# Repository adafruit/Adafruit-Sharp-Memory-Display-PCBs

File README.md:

# PCB for the Adafruit Sharp Memory display breakout board

<br />

[The 96x96 resolution SHARP Memory LCD is no longer made, but we have a higher-resolution 168x144 display available in the shop](https://www.adafruit.com/product/3502).

The 1.3" and 2.7" SHARP Memory LCD displays are a cross between an eInk (e-paper) display and an LCD. They have the ultra-low power usage of eInk and the fast-refresh rates of an LCD. This model has a matt silver background, and pixels show up as little mirrors for a silver-reflective display, a really beautiful and unique look. It does not have a backlight, but it is daylight readable. For dark/night reading you may need to illuminate the LCD area with external LEDs.

The display is 3V powered and 3V logic, so we placed it on a fully assembled & tested breakout board with a 3V regulator and level shifting circuitry. The display slots into a ZIF socket on board and we use a piece of double-sided tape to adhere it onto one side. There are four mounting holes so you can easily attach it to a box.

The display is 'write only' which means that it only needs 3 pins to send data. However, the downside of a write-only display is that the entire 96x96 bits (1,152 bytes) must be buffered by the microcontroller driver. On an Arduino Uno/Leonardo that's half the RAM available and so it might not be possible to run this display with other RAM-heavy libraries like SD interfacing.

Check out [this Learn guide](https://learn.adafruit.com/adafruit-sharp-memory-display-breakout/overview) for details on the boards and usage.

[Then download and install our SHARP Memory Display library](https://github.com/adafruit/Adafruit_SHARP_Memory_Display) and the [Adafruit GFX library](https://github.com/adafruit/Adafruit-GFX-Library). Run the example sharpmemtest sketch with the correct data pins to start drawing lines, circles, rectangles, text, etc!

## License

Adafruit invests time and resources providing this open source design, 
please support Adafruit and open-source hardware by purchasing 
products from Adafruit!

Designed by Adafruit Industries.  
Creative Commons Attribution, Share-Alike license, check license.txt for more information
All text above must be included in any redistribution

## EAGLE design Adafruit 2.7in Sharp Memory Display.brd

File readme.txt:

This is the PCB for the Adafruit Sharp Memory display breakout board
Format is EagleCAD schematic and board layout

For more details, check out the product page at

-----> http://www.adafruit.com/products/1393

Adafruit invests time and resources providing this open source design, 
please support Adafruit and open-source hardware by purchasing 
products from Adafruit!

Designed by Adafruit Industries.  
Creative Commons Attribution, Share-Alike license, check license.txt for more information
All text above must be included in any redistribution

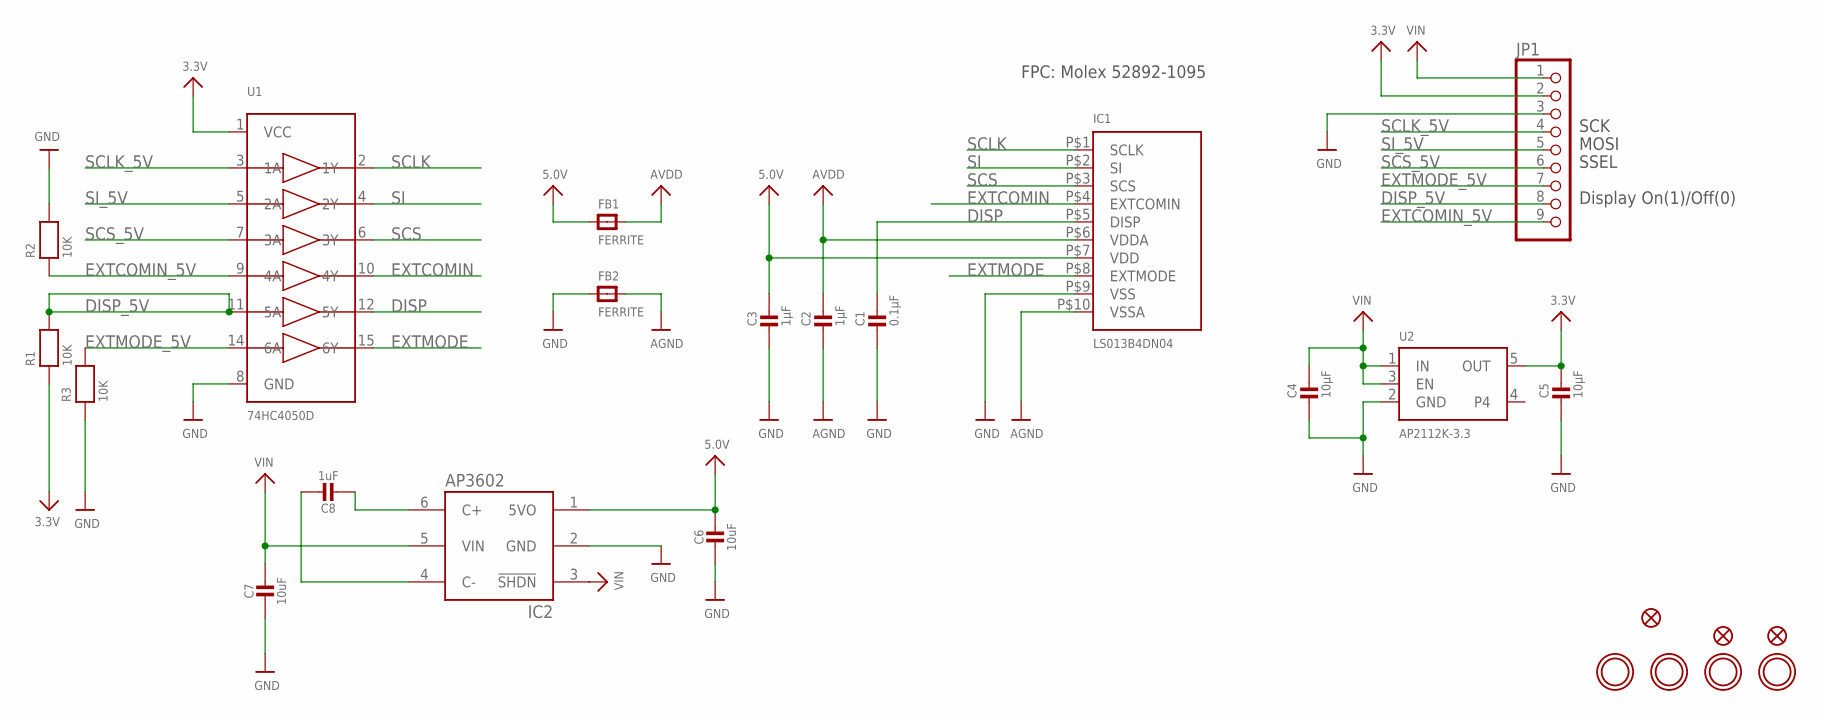
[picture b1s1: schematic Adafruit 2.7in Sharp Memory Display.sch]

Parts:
C1: 0.1µF; 0603-NO
C2: 1µF; 0805_10MGAP
C3: 1µF; 0805-NO
C4, C5: 10µF; 0805-NO
C6, C7: 10uF; 0805-NO
C8: 1uF; 0805-NO
FB1, FB2: FERRITE; _0805
FID1, FID2, FID3: FIDUCIAL_1MM
IC1: LS013B4DN04; SHARP_2.7IN
IC2: AP3602; SOT23-6
JP1: HEADER-1X970MIL; 1X09_ROUND_70
R1, R2, R3: 10K; 0603-NO
U1: 74HC4050D; SOIC16
U2: AP2112K-3.3; SOT23-5
U$21, U$22: MOUNTINGHOLE2.5_THICK; MOUNTINGHOLE_2.5_PLATED_THICK
U$27, U$28: MOUNTINGHOLE2.5; MOUNTINGHOLE_2.5_PLATED

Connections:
3.3V: C5.1, JP1.2, R1.1, U1.1 (VCC), U2.5 (OUT)
5.0V: C3.1, C6.1, FB1.1, IC1.P$7 (VDD), IC2.1 (5VO)
AGND: C2.2, FB2.2, IC1.P$10 (VSSA)
AVDD: C2.1, FB1.2, IC1.P$6 (VDDA)
DISP: C1.1, IC1.P$5 (DISP), U1.12 (5Y)
DISP_5V: JP1.8, R1.2, U1.11 (5A)
EXTCOMIN: IC1.P$4 (EXTCOMIN), U1.10 (4Y)
EXTCOMIN_5V: JP1.9, R2.1, U1.9 (4A)
EXTMODE: IC1.P$8 (EXTMODE), U1.15 (6Y)
EXTMODE_5V: JP1.7, R3.2, U1.14 (6A)
GND: C1.2, C3.2, C4.2, C5.2, C6.2, C7.2, FB2.1, IC1.P$9 (VSS), IC2.2 (GND), JP1.3, R2.2, R3.1, U1.8 (GND), U2.2 (GND)
unnamed: C8.2, IC2.6 (C+)
unnamed: C8.1, IC2.4 (C-)
SCLK: IC1.P$1 (SCLK), U1.2 (1Y)
SCLK_5V: JP1.4, U1.3 (1A)
SCS: IC1.P$3 (SCS), U1.6 (3Y)
SCS_5V: JP1.6, U1.7 (3A)
SI: IC1.P$2 (SI), U1.4 (2Y)
SI_5V: JP1.5, U1.5 (2A)
VIN: C4.1, C7.1, IC2.3 (!SHDN), IC2.5 (VIN), JP1.1, U2.1 (IN), U2.3 (EN)

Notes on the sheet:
SSEL
MOSI
SCK
Display On(1)/Off(0)
FPC: Molex 52892-1095

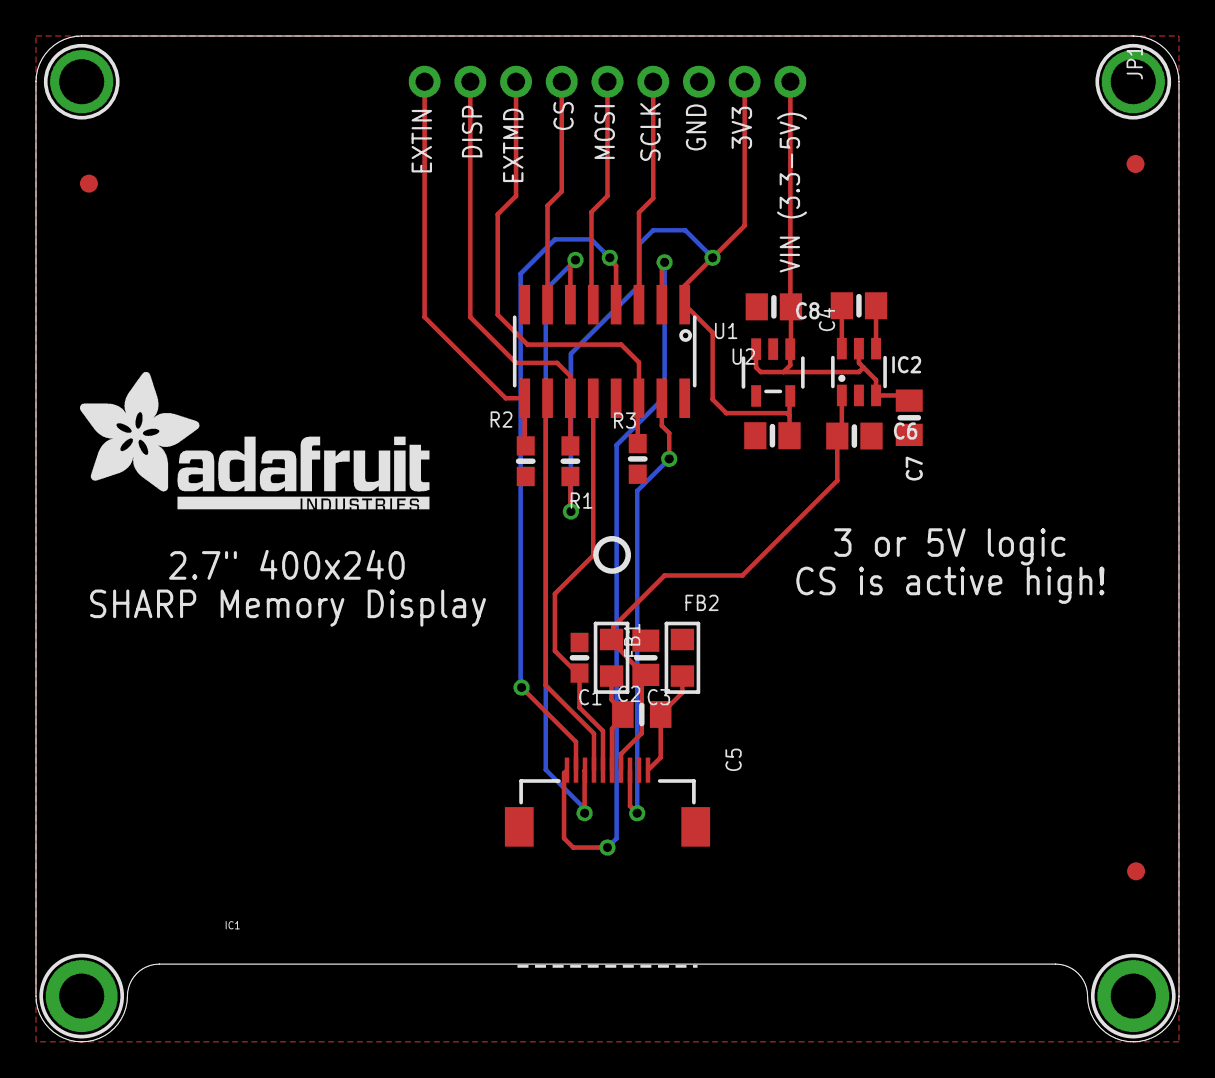
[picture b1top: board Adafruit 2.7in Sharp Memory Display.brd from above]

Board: 2 copper layers, 63.5 x 55.9 mm, 27 parts (0 on the bottom side), 20 nets.

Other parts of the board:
U$29: PCBFEAT-REV-040
U$32: ADAFRUIT_TEXT_20MM

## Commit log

2013-07-25 woo!
2013-07-25 read
2019-04-25 image + readme
2020-08-14 Add asset for 2.7" Sharp Memory Display.
2020-08-14 Adding board files.
2020-08-14 Update README.
